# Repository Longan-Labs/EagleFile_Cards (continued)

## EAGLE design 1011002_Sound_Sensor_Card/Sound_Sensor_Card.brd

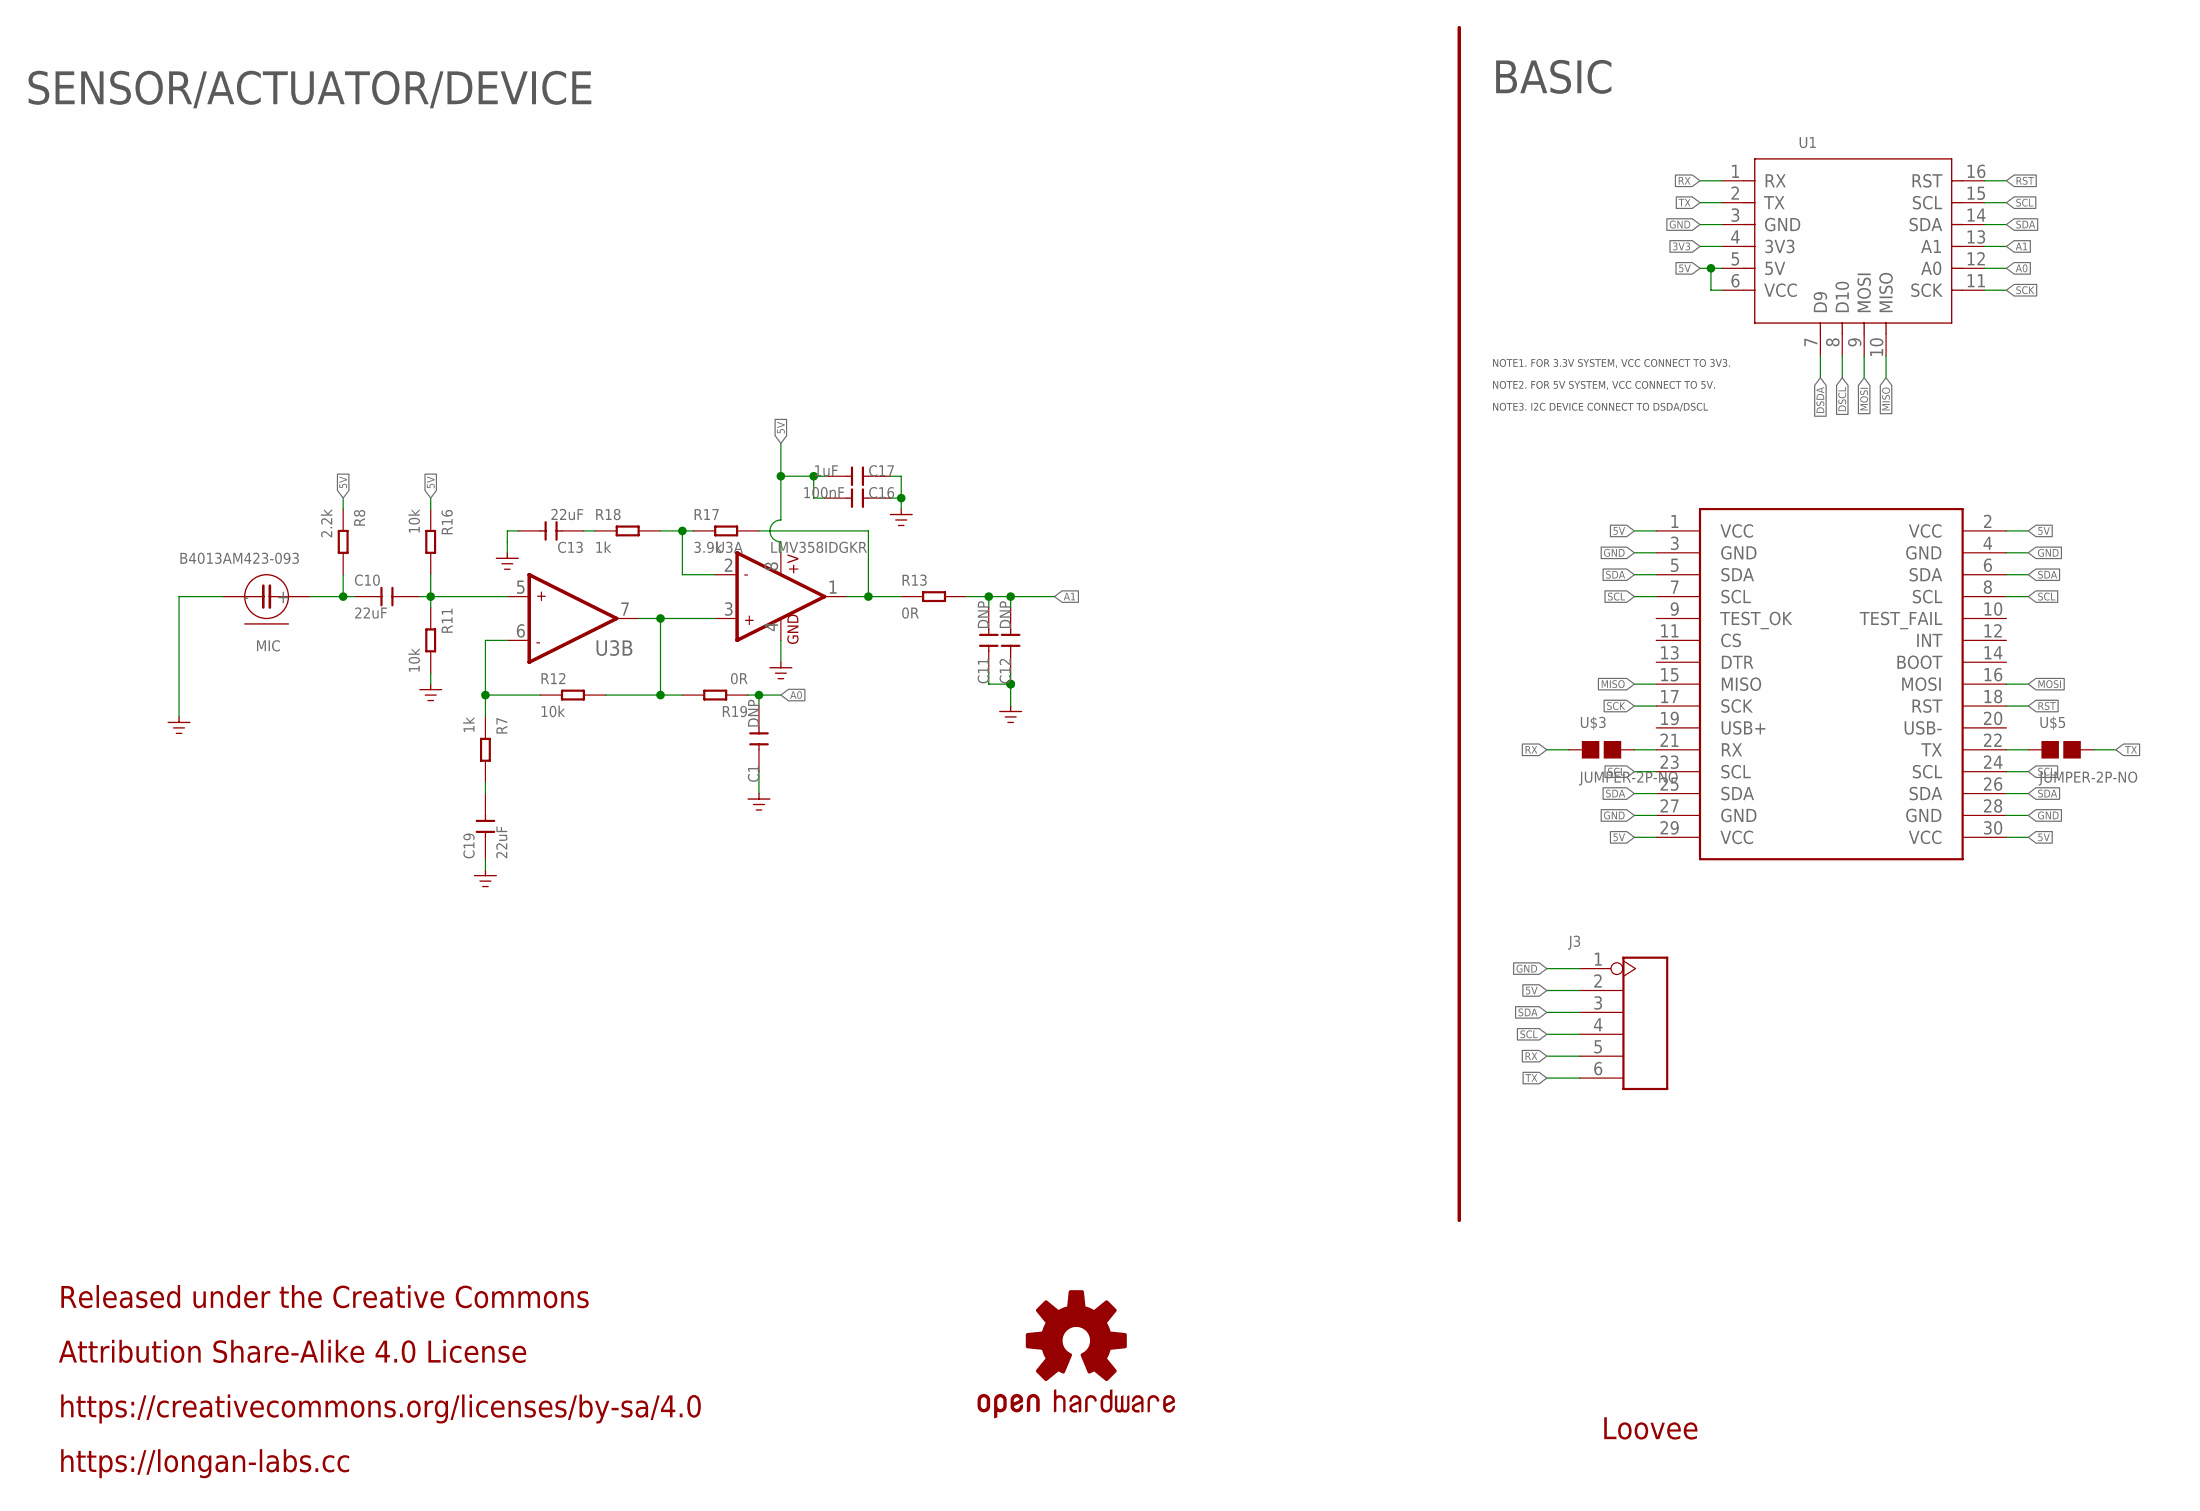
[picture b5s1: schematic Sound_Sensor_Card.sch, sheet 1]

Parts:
C1, C11, C12: DNP; C0603
C10, C13, C19: 22uF; C0603
C16: 100nF; C0603
C17: 1uF; C0603
J3: HEADER-6P-55/35MIL; H6-2.54
LOGO2: OSHW-LOGOS; OSHW-LOGO-S
MIC: B4013AM423-093; MIC2P-SMD-4X4X1.3MM
MOUDLE1: MOUDLE-2X15P-2.54'BOARD'; MOUDLE-2X15P-2.54
R7, R18: 1k; R0603
R8: 2.2k; R0603
R11, R12, R16: 10k; R0603
R13, R19: 0R; R0603
R17: 3.9k; R0603
U1: MOUDLE-CARDS; 16P-2.0-CARDS
U3: LMV358IDGKR; MSOP8-0.65-3X3MM
U$3, U$5: JUMPER-2P-NO; 2P-SMD-NO

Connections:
3V3: U1.4 (3V3)
5V: C16.2, C17.2, J3.2, MOUDLE1.1 (VCC), MOUDLE1.2 (VCC), MOUDLE1.29 (VCC), MOUDLE1.30 (VCC), R8.1, R16.1, U1.5 (5V), U1.6 (VCC), U3.8 (+V)
A0: C1.2, R19.1, U1.12 (A0)
A1: C11.2, C12.2, R13.2, U1.13 (A1)
DSCL: U1.8 (D10)
DSDA: U1.7 (D9)
GND: C1.1, C11.1, C12.1, C13.2, C16.1, C17.1, C19.1, J3.1, MIC.-, MIC.-1 (-), MIC.-2 (-), MIC.-3 (-), MOUDLE1.3 (GND), MOUDLE1.4 (GND), MOUDLE1.27 (GND), MOUDLE1.28 (GND), R11.2, U1.3 (GND), U3.4 (GND)
MISO: MOUDLE1.15 (MISO), U1.10 (MISO)
MOSI: MOUDLE1.16 (MOSI), U1.9 (MOSI)
unnamed: MOUDLE1.21 (RX), U$3.2
unnamed: MOUDLE1.22 (TX), U$5.1
unnamed: C10.1, MIC.+, R8.2
unnamed: C10.2, R11.1, R16.2, U3.5 (+IN2)
unnamed: R12.2, R19.2, U3.3 (+IN1), U3.7 (OUT2)
unnamed: R7.1, R12.1, U3.6 (-IN2)
unnamed: R13.1, R17.2, U3.1 (OUT1)
unnamed: C19.2, R7.2
unnamed: R17.1, R18.2, U3.2 (-IN1)
unnamed: C13.1, R18.1
RST: MOUDLE1.18 (RST), U1.16 (RST)
RX: J3.5, U1.1 (RX), U$3.1
SCK: MOUDLE1.17 (SCK), U1.11 (SCK)
SCL: J3.4, MOUDLE1.7 (SCL), MOUDLE1.8 (SCL), MOUDLE1.23 (SCL), MOUDLE1.24 (SCL), U1.15 (SCL)
SDA: J3.3, MOUDLE1.5 (SDA), MOUDLE1.6 (SDA), MOUDLE1.25 (SDA), MOUDLE1.26 (SDA), U1.14 (SDA)
TX: J3.6, U1.2 (TX), U$5.2

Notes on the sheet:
BASIC
Loovee
NOTE1. FOR 3.3V SYSTEM, VCC CONNECT TO 3V3.
NOTE2. FOR 5V SYSTEM, VCC CONNECT TO 5V.
NOTE3. I2C DEVICE CONNECT TO DSDA/DSCL
SENSOR/ACTUATOR/DEVICE
Released under the Creative Commons
Attribution Share-Alike 4.0 License
https://creativecommons.org/licenses/by-sa/4.0
https://longan-labs.cc

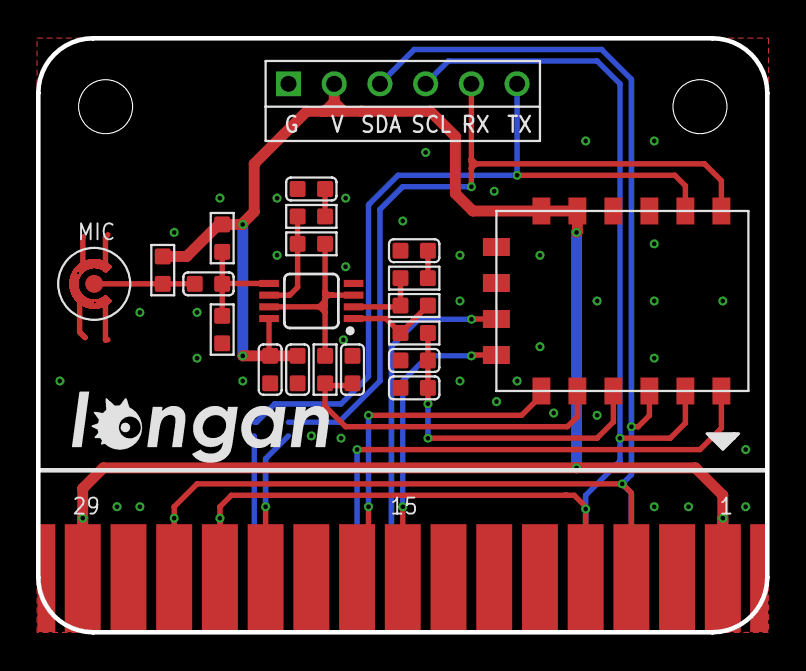
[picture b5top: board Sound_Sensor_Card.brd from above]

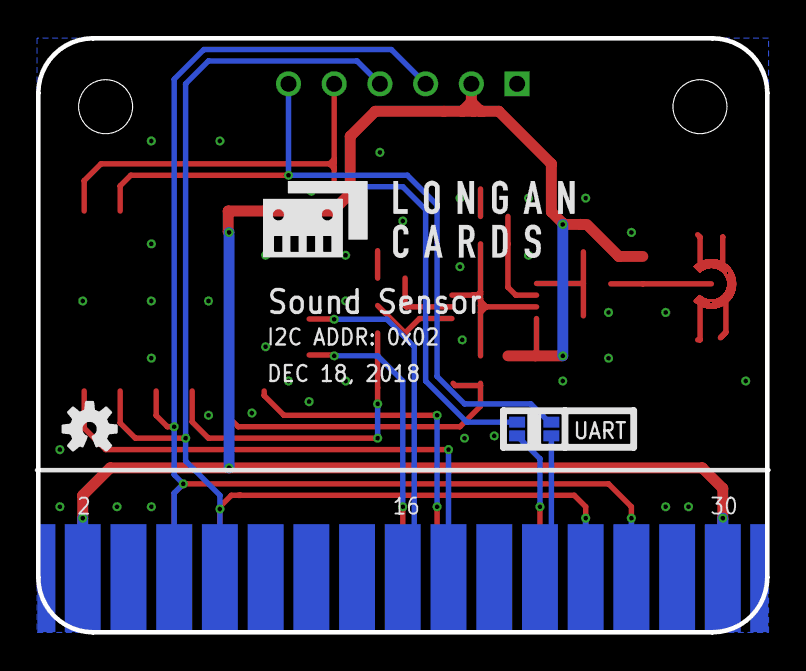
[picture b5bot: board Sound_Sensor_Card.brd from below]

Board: 2 copper layers, 40.5 x 33.0 mm, 27 parts (4 on the bottom side), 22 nets.

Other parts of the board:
U$1: LONGAN-CARDS-MIDDLE
U$2: LONGAN-SILK-SMALLER

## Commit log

2019-04-24 add 25+ boards
